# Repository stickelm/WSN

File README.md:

# IDMI IoT Testbed

## Introduction

The goal of the project is to produce an entire hardware/software suite that lets people configure, control and monitor their places the way they want.

The testbed includes the customized Arduino hardware designed specifically for the smart home/building scenario; a raspberry-pi device acting as an internet gateway for the Arduino devices; a server platform for managing and control those devices and interpret the device data; and, perhaps most importantly, mobile apps for Android and iOS so that you can control all of the smart gadgets/devices from one interface.

You can use the web and mobile apps to control anything that’s connected to the server, whether that’s a lighting system, an IP camera, or the locks on the door. It can become, in short, a remote control and monitor tool for your space.

It was inspired by [Calaos](http://calaos.fr/en/) project.

TO:

Task matrix for assignments (tier 1,2,3,4)
put somewhere public can access

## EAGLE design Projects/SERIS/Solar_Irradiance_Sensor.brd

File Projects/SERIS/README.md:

## SERIS Project

### About

This project is to design a wireless sensor with sun solar irradiance and ambient teperature reading. The device will be placed on the roof top and transimit the measurement data to a remote base station inside a building about 300 meters away.

This project is part of the [NUS SERIS Solar Irradiance Map Project](http://www.solar-repository.sg/irr-map.cfm).

### Components

* Solar Irradiance Sensor ([Si-02-Pt100](http://www.imt-solar.com/products/solar-irradiance-sensor/si-sensor.html))

Wirings of the sensor:

 Color | Description
--- | --- | ---
Orange | 55, 3 mV/(1000W/qm)
Yellow, Red | PT100
Green, Brown | PT100
Black | 0 VDC

* [Libelium Waspmote V1.2](http://www.libelium.com/products/waspmote/)

* Digi XBee-PRO 900HP (900 MHz RF Module  [XBP9B-DPST-041](http://www.digi.com/products/wireless-wired-embedded-solutions/zigbee-rf-modules/point-multipoint-rfmodules/xbee-pro-900hp#overview))

* Various Electronic Components (BOM)
    * 100k, 2k resistors (0.1%)
    * LM324N IC (DIP14)
    * 0.1uF Ceramic Capacitor
    * MAX31865 IC RTD Temperature Digital Converter Board
    * Pinhead and Female pinheader connector
    * [Screw terminal blocks](https://www.sparkfun.com/products/10571) (2-pin, 2.54mm pitch)
    * Double side prototype board (5cm x 7cm)

## Circuit Design

It is based on the code and circuit in the folder [Solar Irradiance Sensor](https://github.com/xianlin/WSN/tree/master/Sensors/Solar%20Irradiance) and [RTD Temperature Sensor](https://github.com/xianlin/WSN/tree/master/Sensors/Temperature). The prototype board/shield can be directly plugged onto the Libelium waspmote device.

## Software

### Xbee Frame

XBee received frame details
```
Receive Packet (API 2)

7E 00 4C 90 00 7D 33 A2 00 40 C3 69 3F FF FE 41 3C 3D 3E 80 04 23 33 38 37 32 33 35 31 36 34 23 4E 30 31 23 31 35 33 23 54 49 4D 45 3A 31 34 2D 34 39 2D 33 33 23 42 41 54 3A 36 39 23 54 43 41 3A 33 35 2E 39 31 23 50 41 52 3A 38 2E 36 35 23 E4

    - Start delimiter: 7E
    - Length: 00 4C (76)
    - Frame type: 90 (Receive Packet)
    - 64-bit source address: 00 13 A2 00 40 C3 69 3F
    - 16-bit source address: FF FE
    - Receive options: 41
    - Received data: 3C 3D 3E 80 04 23 33 38 37 32 33 35 31 36 34 23 4E 30 31 23 31 35 33 23 54 49 4D 45 3A 31 34 2D 34 39 2D 33 33 23 42 41 54 3A 36 39 23 54 43 41 3A 33 35 2E 39 31 23 50 41 52 3A 38 2E 36 35 23
    - Checksum: E4
```

Received data convert from Hex to ASCII
```
    <=>#387235164#N01#153#TIME:14-49-33#BAT:69#TCA:35.91#PAR:8.65#
```

[Python scripts](https://github.com/xianlin/WSN/blob/master/Projects/SERIS/pylink.py) read serial port and upload data to the cloud

```
# run script at background when restart raspberry pi
sudo vi /etc/rc.local
nohup python /home/pi/scripts/python/pylink.py >/tmp/output.txt 2>&1 &
```

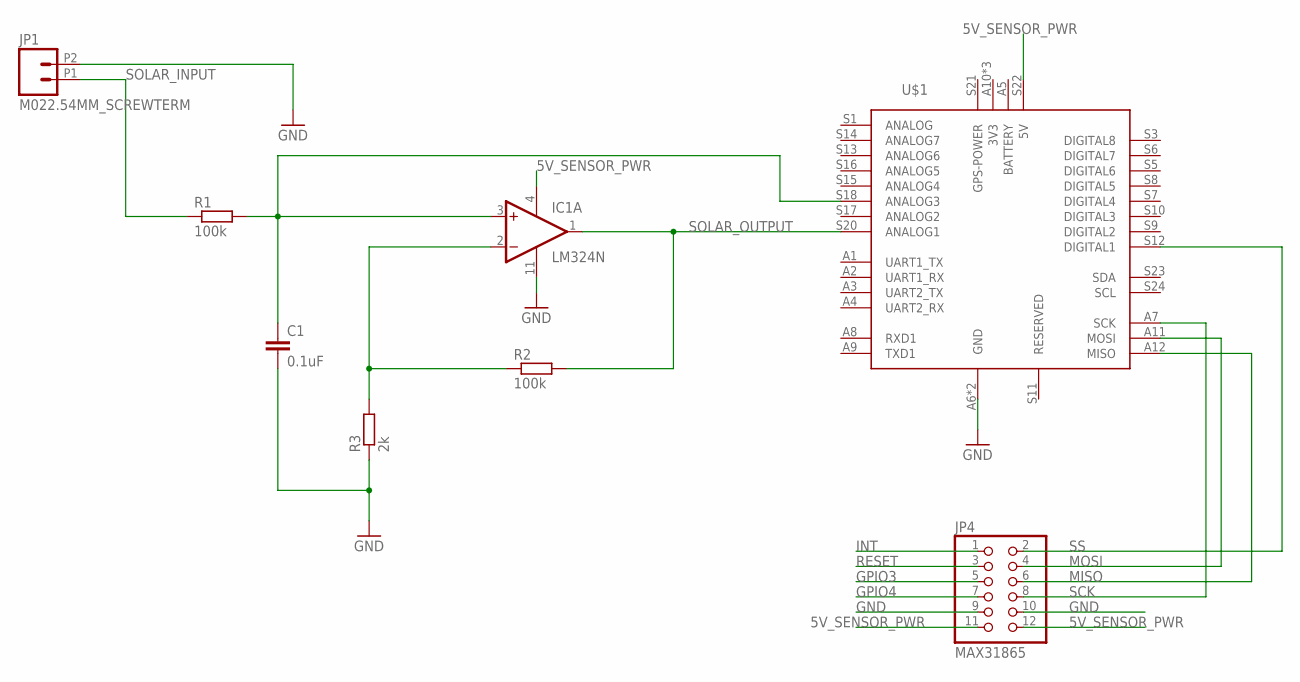
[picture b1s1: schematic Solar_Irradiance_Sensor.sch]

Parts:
C1: 0.1uF; C025-024X044
IC1: LM324N; DIL14
JP1: M022.54MM_SCREWTERM; 1X02_2.54_SCREWTERM
JP4: MAX31865; 2X06
R1, R2: 100k; 0207/10
R3: 2k; 0207/10
U$1: WASP

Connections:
5V_SENSOR_PWR: IC1.4 (V+), JP4.11, JP4.12, U$1.S22 (5V)
GND: C1.2, IC1.11 (V-), JP1.P2 (2), JP4.9, JP4.10, R3.1, U$1.A6 (GND), U$1.S4 (GND)
GPIO3: JP4.5
GPIO4: JP4.7
INT: JP4.1
MISO: JP4.6, U$1.A12 (MISO)
MOSI: JP4.4, U$1.A11 (MOSI)
unnamed: IC1.2 (-IN), R2.1, R3.2
unnamed: C1.1, IC1.3 (+IN), R1.2, U$1.S18 (ANALOG3)
RESET: JP4.3
SCK: JP4.8, U$1.A7 (SCK)
SOLAR_INPUT: JP1.P1 (1), R1.1
SOLAR_OUTPUT: IC1.1 (OUT), R2.2, U$1.S20 (ANALOG1)
SS: JP4.2, U$1.S12 (DIGITAL1)

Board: 2 copper layers, 8 parts (0 on the bottom side), 10 nets, no tracks yet.

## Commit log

2014-06-18 my first commit
2014-06-18 readme changed
2014-06-18 changed readme
2014-06-19 Create MeshliumDB_table_sample
2014-06-19 Update and rename meshlium_config to meshlium_file_system
2014-06-19 Update MeshliumDB_table_sample
2014-06-19 Update and rename meshlium_file_system to meshlium_system_info
2014-06-19 Update meshlium_system_info
2014-06-19 added api folder
2014-06-19 added manager system
2014-06-19 update index into sensorParser table
2014-07-22 added sensor reading API
2014-07-22 added web files
2014-07-22 moved image file to img folder
2014-07-22 changed index.html
2014-07-22 changed css and js
2014-07-22 added jquery nusmap.js
2014-07-23 added sensor_process.php
2014-07-29 no message
2014-07-30 Create otap_del
2014-07-30 Rename README.MD to README.md
2014-07-30 Rename otap_del to otap_del.sh
2014-07-30 Rename otap_del.sh to otap_del_all.sh
2014-07-30 Create wasp_id_mac
2014-07-30 Update wasp_id_mac
2014-07-31 changed sensor.php to api.php
2014-08-03 modifed api.php
2014-08-04 html with line chart done
2014-08-04 updated ajax post at api.php
2014-08-05 moved meshlium rest arcgis plugin to Web directory
2014-08-06 heatmap done
2014-08-11 modified api.php
2014-08-20 css changes
2014-08-21 bootstrap development
2014-08-22 ldap login draft
2014-12-01 LTspice amplifier circuit simulation results for PT100 temperature sensor
2014-12-01 trendline formula updated
2014-12-01 added 4 wire connection
2014-12-01 added solar irradiance amplifier circuit and simulation results
2014-12-02 updated solar irrandiance readme
2014-12-04 updated folder structure
2014-12-04 added waspmote wireless send/receive code
2014-12-07 xbee test ino file added
2014-12-07 xbee change configuration via andriuno AT command
2014-12-09 added various files (solar irradiance circuit)
2014-12-09 send xbee at command
2014-12-09 moved files
2014-12-09 eagle circuit update SERIS
2014-12-10 updated waspmote SERIS code
2014-12-14 updated wireless readme
2014-12-16 updated waspmote 900MHz
2014-12-19 updated SERIS project
2014-12-20 updated SERIS 900MHz
2014-12-23 updated enclosure
2014-12-25 otap updated for S3B
2014-12-25 changed folder structure
2014-12-25 900_S3B_Send_Sensor
2014-12-25 updated sending S3B
2014-12-26 updated send
2014-12-27 xbee python update
2014-12-29 pylink updated to emoncms
2014-12-30 updated OTAP with SERIS project
2014-12-31 moved/deleted files
2015-01-01 updated with new otap settings
2015-01-05 updated dual radio
2015-01-16 added xbee as sensors
2015-01-21 added rasp
2015-02-06 moved libelium directory to a new repo
2015-02-06 moved Enclosure directory
2015-04-15 Update XBee_IO_Sample.js
    added motion sensor
2015-05-22 Update _900_S3B_Send_Sensor_Reading.pde
    update to new API 1.5

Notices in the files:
parts and their libraries:
SparkFun-Connectors: Licensing: Creative Commons ShareAlike 4.0 International - https://creativecommons.org/licenses/by-sa/4.0
